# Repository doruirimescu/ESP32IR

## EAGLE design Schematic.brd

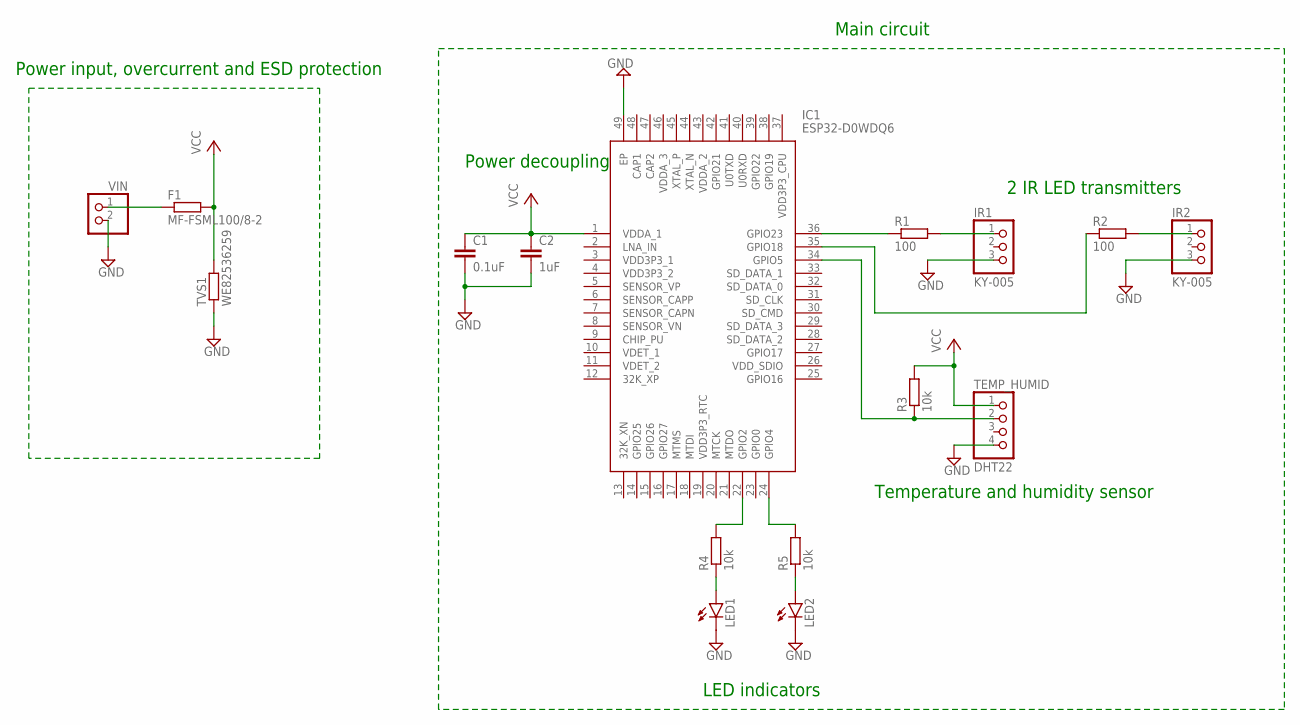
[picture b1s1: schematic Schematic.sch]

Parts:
C1: 0.1uF; C0805
C2: 1uF; C0805
F1: MF-FSML100/8-2; R0603
IC1: ESP32-D0WDQ6; QFN40P600X600X90-49N
IR1, IR2: KY-005; 1X03
LED1, LED2: LED3MM
R1, R2: 100; 0207/12
R3, R4, R5: 10k; 0207/12
TEMP_HUMID: DHT22; 1X04
TVS1: WE82536259; R0603
VIN: PINHD-1X2; 1X02

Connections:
GND: C1.2, C2.2, IC1.49 (EP), IR1.3, IR2.3, LED1.K (C), LED2.K (C), TEMP_HUMID.4, TVS1.1, VIN.2
unnamed: IR1.1, R1.2
unnamed: IC1.36 (GPIO23), R1.1
unnamed: IR2.1, R2.2
unnamed: IC1.35 (GPIO18), R2.1
unnamed: IC1.34 (GPIO5), R3.1, TEMP_HUMID.2
unnamed: LED2.A, R5.1
unnamed: LED1.A, R4.1
unnamed: IC1.22 (GPIO2), R4.2
unnamed: IC1.24 (GPIO4), R5.2
unnamed: F1.1, VIN.1
VCC: C1.1, C2.1, F1.2, IC1.1 (VDDA_1), R3.2, TEMP_HUMID.1, TVS1.2

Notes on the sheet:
Power input, overcurrent and ESD protection
Main circuit
LED indicators
Temperature and humidity sensor
2 IR LED transmitters
Power decoupling

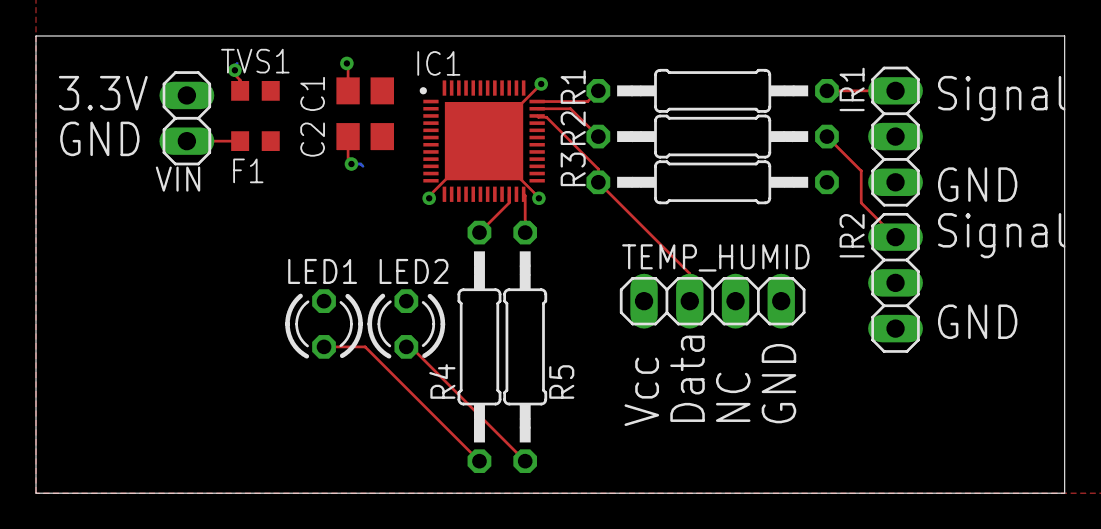
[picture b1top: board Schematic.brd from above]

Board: 2 copper layers, 57.1 x 25.4 mm, 16 parts (0 on the bottom side), 12 nets.

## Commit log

2019-07-28 Add files via upload
    ESP32 with IR, Temperature, Humidity and indicator LEDs
